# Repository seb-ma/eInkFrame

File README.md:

# Weather station e-ink frame

This is a project (hardware and software parts) designed to have a full Weather station (and many more features) displayed on a e-ink screen put in a photo frame with tactile buttons.

It is done with a Raspberry Pi, a 7.8" e-ink screen, a capacitive touch sensor, a temperature/humidity/pressure/gas sensor and needs a internet connection.

## Status

This project is fully functional.

Some improvements can be done (see [MagicMirror² Installation](software.md#Disclaimer)) and more features may be added in the future (see below).

## Hardware

Complete guide is in [hardware part](hardware.md).

It includes:
- Information on schematic
- Bill Of Material

## Software

Complete guide is in [software part](software.md).

It includes:
- Installation and configuration of OS on Raspberry
- Installation and configuration of [MagicMirror²](https://magicmirror.builders/) and all the modules

## Features

At this stage, all the ticked features are available (the other features may never be done).
It can also be customized by adding new modules (see [MagicMirror² Installation](software.md#MagicMirror²)).

### Basic

- [X] Current day and time
- [X] sunrise/sunset
- [X] moonrise/moonset
- [X] Gain/loss of sun minutes since yesterday
- [X] Moon phase
- [X] Saint of the day

### Weather/outdoor

- [X] Indoor sensors:
  - [X] temperature
  - [X] humidity
  - [X] pressure
  - [X] air quality
- [X] Current weather with:
  - [X] temperature
  - [X] feel-like temperature
  - [X] humidity
  - [X] pressure
  - [X] wind
  - [X] UV index
  - [X] rain probability
  - [X] air quality
- [X] Graph of weather forecast for next days with:
  - [X] temperature
  - [X] feel-like temperature
  - [X] min/max temperature
  - [X] rain and snow
  - [X] weather icon
  - [X] humidity
  - [X] pressure
  - [X] wind
  - [X] UV index
  - [X] rain probability
  - [X] air quality
  - [ ] same curves for previous days
- [X] Alerts on the risk of rain, wind, ice...
- [X] Alerts on current active allergens
- [ ] Maps of winds, rain, lightning
- [ ] Historic graph of indoor sensor measures

### Calendar and tasks

- [X] Upcoming events in family calendar
- [X] Upcoming birthdays
- [X] Tasks (from Trello)

### Travels

- [X] Next upcoming used bus lines
  - [X] with alerts on this lines
- [X] Travel time to work
- [ ] Map of traffic
- [ ] Traffic for the next event in calendar

### Entertainment

- [X] Headlines of news
- [X] Current Spotify music (watch multiple accounts)
  - [X] with buttons for Spotify control (volume, next/previous, start/stop)
- [ ] Game of life

### Display

- [X] Different pages that can be accessed with buttons

### Advanced features (not yet planned)

- [ ] [Home Assistant](https://www.home-assistant.io/) interaction
- [ ] Communication with home sensors (indoor and outdoor)

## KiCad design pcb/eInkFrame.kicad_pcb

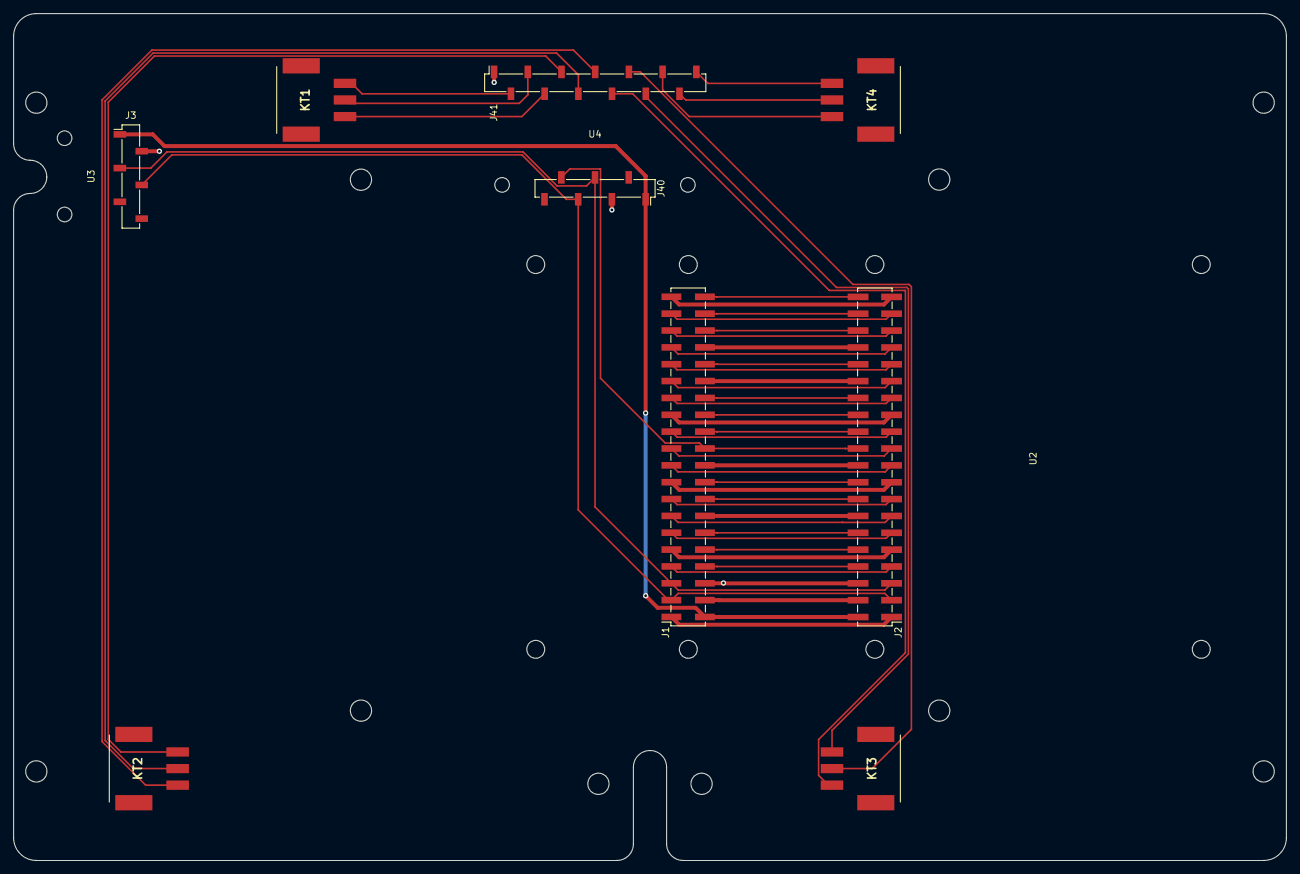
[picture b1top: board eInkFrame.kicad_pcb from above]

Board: 2 copper layers, 191.8 x 127.7 mm, 24 parts (1 on the bottom side), 52 nets.

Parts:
E2: Screen; Waveshare eink 7.8
H1, H2, H3, H4, H5, H6: M3; MountingHole_3.2mm_M3
HF1, HF2, HF3, HF4: M3; MountingHole_3.2mm_M3
J1: Socket Raspberry; PinSocket_2x20_P2.54mm_Vertical_SMD
J2: Socket IT8951; PinHeader_2x20_P2.54mm_Vertical_SMD
J3: Socket BME680; PinSocket_1x06_P2.54mm_Vertical_SMD_Pin1Left
J40: Socket MPR121 comm; PinSocket_1x07_P2.54mm_Vertical_SMD_Pin1Right
J41: Socket MPR121 contacts; PinSocket_1x13_P2.54mm_Vertical_SMD_Pin1Right
KT1, KT2, KT3, KT4: Terminal_01x03; Phoenix contact 1814647
U1: Raspberry; Raspberry uHAT (Socket)
U2: IT8951_Driver; IT8951 driver HAT (Socket)
U3: CJMCU-680; CJMCU-680 HAT (Socket)
U4: MPR121; Adafruit MPR121 (Socket)

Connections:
/G1: J1.1 (3v3), J2.1
/G4: J1.4 (5V), J2.4
/G7: J1.7 (gpio_4), J2.7
/G8: J1.8 (gpio_14), J2.8
/G9: J1.9 (Gnd), J2.9
/G10: J1.10 (gpio_15), J2.10
/G11: J1.11 (gpio_17), J2.11
/G12: J1.12 (gpio_18), J2.12
/G13: J1.13 (gpio_27), J2.13
/G14: J1.14 (Gnd), J2.14
/G15: J1.15 (gpio_22), J2.15
/G16: J1.16 (gpio_23), J2.16
/G17: J1.17 (3v3), J2.17
/G18: J1.18 (gpio_24), J2.18
/G19: J1.19 (SPI0_MOSI), J2.19
/G20: J1.20 (Gnd), J2.20
/G21: J1.21 (SPI0_MISO), J2.21
/G23: J1.23 (SPI0_SCLK), J2.23
/G24: J1.24 (SPI0_CE0), J2.24
/G25: J1.25 (Gnd), J2.25
/G26: J1.26 (SPI0_CE1), J2.26
/G27: J1.27 (gpio_0), J2.27
/G28: J1.28 (gpio_1), J2.28
/G29: J1.29 (gpio_5), J2.29
/G30: J1.30 (Gnd), J2.30
/G31: J1.31 (gpio_6), J2.31
/G32: J1.32 (gpio_12), J2.32
/G33: J1.33 (gpio_13), J2.33
/G34: J1.34 (Gnd), J2.34
/G35: J1.35 (gpio_19), J2.35
/G36: J1.36 (gpio_16), J2.36
/G37: J1.37 (gpio_26), J2.37
/G38: J1.38 (gpio_20), J2.38
/G39: J1.39 (Gnd), J2.39
/G40: J1.40 (gpio_21), J2.40
GND: J1.6 (Gnd), J2.6, J3.2, J40.3, J41.1
MPR121_INT: J1.22 (gpio_25), J2.22, J40.6
unnamed: J41.2, KT1.1
unnamed: J41.3, KT1.2
unnamed: J41.4, KT1.3
unnamed: J41.5, KT2.1
unnamed: J41.6, KT2.2
unnamed: J41.7, KT2.3
unnamed: J41.8, KT3.1
unnamed: J41.9, KT3.2
unnamed: J41.10, KT3.3
unnamed: J41.11, KT4.1
unnamed: J41.12, KT4.2
unnamed: J41.13, KT4.3
SCL: J1.5 (SCL), J2.5, J3.3, J40.4
SDA: J1.3 (SDA), J2.3, J3.4, J40.5
VIN: J1.2 (5V), J2.2, J3.1, J40.1

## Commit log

2022-03-07 All preparations (hardware & software files + guide)
2022-03-08 Rework patch creation + various corrections
2022-03-19 Global doc cleanup, pcb and scripts enhancement, adding images
2022-03-23 Adjustements with firsts runs
2022-03-26 Screen readability improvement, adding hardware tests, update script correction
2022-03-28 Change a hard to source component and adapt PCB accordingly + hide some Spotify elements + global formatting
2022-04-03 New PCB stand, adding photos, minor updates after final mounting
2022-04-08 Set in 4-levels gray most of the modules, define each button function, move VigilanceMeteoFrance to left and limit its width
2022-04-09 weather: UV and precipitation probability + minor typo and formatting
2022-04-11 Add mmm-weatherproviderunique + needed config, hide traffic header when module is hidden
2022-04-12 More robust patch application
2022-04-16 Add AQI on current weather
2022-04-27 Add patch to MMM-VigilanceMeteoFrance, update MMM-NotifCustomActions config, add holidays ics
2022-04-27 Remove no more needed patch on missing require
2022-04-27 Upgrade to nodejs v17: installation guide + related ajustments
2022-05-01 Reference free icons of fontawesome
2022-05-02 Use cache on nunjucks template files
2022-05-09 Adapt config according to various modules updates
2022-05-09 Add missing patch on openweather provider
2022-05-24 Better patch on Trello hide/show + Correction in pollution retrieving
2022-10-03 Add instruction for update + udpate MPR121 module dependencies
2023-02-05 Changes to comply MagicMirror² 2.22.0
2023-02-05 Update needed dependencies + correction on installation script
2023-02-05 Script without stashing
2023-02-05 Correction to beaufort unit
2023-03-07 Remove cups from running services
2023-04-07 Change precipitation configuration of MMMM-WeatherChart3D (induced by MagiMirror² v2.23.0)
2023-05-06 Keep correct locale for moment.js + correction on CSS (due to upgrade 2.23)
2023-07-16 Add npm update before install on modules with specific dependecies
2023-08-06 Update added dependencies in patch and set correct locale
2023-08-06 Add chromium to install
2023-10-08 Changes to comply MagicMirror² 2.25.0
2023-10-08 Update dependencies of MPR121 + Remove LOG level in default logs
2023-10-13 Improve installation procedure from scratch
2023-10-29 Correction in apt install dependencies
2023-11-04 Remove no more needed colors (already provided by module)
2024-08-03 Add heartbeat script
2024-08-03 Update patches to comply with last releases
2024-08-03 Remove MMM-Freebox-Monitor patch
2024-08-03 Update authentication for MMM-VigilanceMeteoFrance
